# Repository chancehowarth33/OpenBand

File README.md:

<p align="center">
  <picture>
    <source media="(prefers-color-scheme: dark)" srcset="images/logo-dark.png">
    
  </picture>
</p>

<p align="center"><b>Open Source WHOOP.</b></p>

<p align="center">
  An open-source, screenless wearable health tracker built from scratch: custom PCB, custom
  firmware, custom enclosure, custom iOS app. It reads heart rate, blood oxygen, and steps off
  your wrist and streams them to your phone over Bluetooth.
</p>

---

## Why I built this

I wanted to know whether I could build a real consumer wearable end to end, by myself, rather
than wiring a dev board to a breakout sensor and calling it a project. That means every layer,
schematic capture, a two-layer board with an RF section that actually works, hand assembly,
bare-metal bring-up, an RTOS, sensor drivers written against datasheets, the signal processing
that turns raw photodiode counts into a heart rate, a Bluetooth GATT server, a printed
enclosure, and a native phone app to display it all.

WHOOP is the reference point because it has the same architecture as what I wanted to build: no
screen, no buttons, worn continuously on a strap, with all the intelligence in the sensors and
all the interface on your phone. That constraint is what makes it interesting. There is no
display to hide behind, so the device either produces trustworthy numbers or it does not.

It works. Heart rate, SpO2, steps, and battery all read correctly on hardware I designed and
soldered, and stream live to an app I wrote. Everything needed to build one is in this repo:
schematics, board layout, fabrication outputs, firmware, enclosure models, the full bill of
materials, and the iOS app.

### What it tracks

| Metric | Source | How |
|--------|--------|-----|
| **Heart rate** | MAX30102 PPG | Autocorrelation on the IR waveform (40–200 bpm band), quality-gated by perfusion index |
| **Blood oxygen (SpO2)** | MAX30102 PPG | Red/IR AC-to-DC ratio-of-ratios |
| **Steps** | BMI270 IMU | Onboard hardware step counter, with a software pedometer fallback |
| **Battery** | ADC divider | 100 kΩ / 220 kΩ divider off the LiPo rail |

All four stream to the phone over BLE every 2 seconds.

---

## The device

OpenBand is worn on the wrist with a standard strap. The electronics are a single ~38 mm
circular board that drops into a 3D-printed enclosure; the strap threads through slots on either
side, and four M1.6 screws retain the board from below. A cutout in the bottom of the case
exposes the optical sensor so it sits directly against the skin and has to be in firm, consistent contact with the wrist or the
pulse waveform disappears into noise.

The top shell holds the board in a circular pocket with a strap slot on each side. The bottom
retains it with four screws and exposes the MAX30102 window in the center.

The enclosure is OpenSCAD, in [`case/`](case), and went through two revisions. V1 taught me
most of what was wrong with it. The interior needed to be a true circle because the strap mounts
were intruding on the board pocket, the sensor window was slightly too small, the screw holes
were undersized for M1.6 threads, the programming-header opening did not line up with the pins,
and the outer wall of the strap slot was too thin to survive being worn. V2 fixed all of it.

---

## PCB design

A two-layer circular PCB, roughly 38 mm across, with a cutout at the bottom edge for strap
clearance and four mounting holes for the enclosure screws.

### 3D renders

**Front side.** The CYBLE-416045-02 BLE module dominates the center of the board with its MIFA
antenna exposed along the top edge, deliberately kept clear of copper pours for RF performance.
The BMI270 IMU sits bottom-left, the 32.768 kHz RTC crystal is top-left, and the LiPo charger IC
(U4_CHAR1), 1.8 V LDO (U5_1P8), and supporting passives are packed along the right edge. The SWD
programming header (JPROG1) and the battery/charger pads are on the left and bottom-right.

**Back side.** The MAX30102 optical heart rate and SpO2 sensor (U2_MAX1) is mounted on the back
of the board, facing down toward the skin when worn. Putting it on this side keeps the optical
window unobstructed and in direct contact with the wrist. Its decoupling capacitors are grouped
tightly around it to keep switching noise off the LED drive lines.

### Routing

**Front copper (F.Cu).** Red traces carry the I2C bus (SDA/SCL) from the CYBLE module out to the
BMI270 and down through vias to the MAX30102 on the back. The RTC lines route separately to
avoid crosstalk. Power distribution fans out from the LDO and charger on the right side.

**Back copper (B.Cu).** The back layer is kept deliberately sparse, primarily the I2C and power
connections to the MAX30102 plus the battery and charger fanout. The copper-free keepout under
the CYBLE module's antenna extends through both layers.

---

## Assembled hardware

**Bring-up ("proof of life").** The fully populated board running off a LiPo cell on the bench
with the green status LED lit. This was the first power-on test, confirming the CYBLE module,
LDO, and charger all came up correctly before any firmware was flashed.

**Size in hand.** The bare board for scale, with the battery leads attached.

**Assembled front.** The CYBLE-416045-02 and its gold MIFA antenna at the top, the BMI270 IMU
(U1_IMU1) and RTC crystal (RTC1) on the left, the SWD header (JPROG1) on the far left, and the
1.8 V LDO (U5_1P8) plus battery (BATT) and charger (CHAR) pads down the right side.

**Assembled back.** The skin-facing side, dominated by the MAX30102 optical HR/SpO2 sensor
(U2_MAX1) in the center, its window sitting flush against the wrist.

---

## Firmware

Built with **Infineon ModusToolbox** against the **CY8CPROTO-063-BLE** BSP (the same PSoC 6 BLE
part inside the CYBLE-416045-02 module), running **FreeRTOS**. Application code runs on the
Cortex-M4; the Cortex-M0+ runs the BLESS Bluetooth link-layer controller.

```
main.c
  └─ system_control_initialize()
       ├─ I2C init (SCB3, P6_4 SCL / P6_5 SDA, 400 kHz)
       ├─ i2c_mutex (recursive, shared by all sensor tasks)
       ├─ task_max30102        PPG FIFO → health_algo
       ├─ task_bmi270          6-axis IMU + hardware step counter
       ├─ task_sw_steps        software pedometer (SW_STEP_COUNTER builds only)
       ├─ task_system_control  prints health metrics every 2 s
       └─ task_ble             WICED BT stack + GATT notifications every 2 s
```

Both sensors share one 400 kHz I2C bus (MAX30102 at `0x57`, BMI270 at `0x68`), arbitrated by a
recursive mutex. Results land in `health_hr`, `health_spo2`, `health_steps`, and
`health_battery`, which the reporting and BLE tasks consume.

The parts I am most pleased with:

- **The signal processing runs on the device, not the phone.** `health_algo.c` does DC removal
  and moving-average smoothing, then finds heart rate by autocorrelation, looking for the
  strongest self-similarity lag in the 40 to 200 bpm band, with a threshold peak detector as a
  cross-check. A perfusion-index quality gate means a motion-corrupted window holds the last
  good value instead of confidently reporting garbage. SpO2 comes from the Red/IR ratio-of-ratios.
- **Power management is gated on the phone connection.** In `LOW_POWER` builds the optical
  sensor is fully shut down whenever no phone is connected, and runs live only while the app is
  connected, since HR and SpO2 only matter when someone is looking at them. Steps keep counting
  either way. With gyro-off, adaptive LED drive, shorter LED pulses, and slow BLE advertising and
  connection parameters, measured draw goes from about 12 mA to about 9 mA.
- **The step counter diagnoses itself.** The BMI270 needs an 8 KB configuration blob loaded over
  I2C at boot, which is by far the most demanding transfer on the bus, so the loader retries with
  a soft reset up to five times rather than bricking the task on a bad load. One of my boards
  appeared to have a dead feature engine, so I wrote a pure-software accelerometer pedometer
  (`SW_STEP_COUNTER`) as a drop-in replacement. The root cause turned out to be a cold solder
  joint, and re-reflowing the part fixed it, but the fallback stayed in.

Full detail, including the low-power measurements and the complete BMI270 debugging trail, is in
[`software/README.md`](software/README.md).

### BLE services

| Service | Characteristics |
|---------|-----------------|
| WatchWise Health (custom 128-bit) | SpO2 (read + notify), StepCount (read + notify, uint32 LE) |
| Heart Rate (`0x180D`) | HR Measurement (`0x2A37`) |
| Battery (`0x180F`) | Battery Level (`0x2A19`) |

Custom UUIDs: service `5E021176-5E66-483F-AE53-D3291D2CC787`, SpO2
`F1F72B4B-1D76-43A3-ADB2-0E04905ACC8F`, StepCount `C36072C1-2706-41F1-8D28-E0619FE31FFA`.

Heart rate and battery use the standard SIG-assigned services, so the device also works with any
generic BLE tool (nRF Connect shows it as `WatchWise2`) if you would rather not build the app.

---

## iOS app

A native **SwiftUI + CoreBluetooth** dashboard that auto-scans, connects, and streams live heart
rate, SpO2, steps, and battery, with a heart-rate trend line. It needs Xcode 16+ and a real
iPhone on iOS 17+, since BLE does not work in the Simulator. A free Apple ID is enough for 7-day
signing.

One detail worth mentioning: the firmware reports a *cumulative* step count that resets to zero
whenever the device reboots, so "today's steps" cannot just be the raw value. `StepTracker.swift`
tracks the counter's baseline and handles the reset case.

Build and signing steps are in
[`software/mobile/WatchWiseApp/README.md`](software/mobile/WatchWiseApp/README.md).

---

## Repository structure

```text
OpenBand/
├── pcb/                             # Board design
│   ├── altium_project/              # Altium project, schematic sheets, 3D
│   ├── watchwise_main_kicad/        # KiCad schematic + layout, JLCPCB outputs
│   └── assembly.txt                 # Assembly notes
│
├── software/
│   ├── README.md                    # Full firmware documentation
│   ├── firmware/                    # ModusToolbox firmware project
│   │   ├── Makefile                 # Build system, programming reset-pulse override
│   │   ├── bsps/                    # CY8CPROTO-063-BLE BSP + BT Configurator output
│   │   └── app/FreeRTOS/tasks/src/
│   │       ├── task_system_control.c    # I2C/UART init, task spawning, reporting
│   │       ├── task_max30102.c          # PPG driver + power scheduling
│   │       ├── task_bmi270.c            # IMU driver + hardware step counter
│   │       ├── sw_step_counter.c        # Software pedometer fallback
│   │       ├── task_ble.c               # WICED BT stack, GATT, notifications
│   │       ├── health_algo.c            # HR / SpO2 signal processing
│   │       └── ww_rtc.c                 # RTC
│   ├── mobile/WatchWiseApp/         # SwiftUI + CoreBluetooth iOS app
│   └── BMI270_debug.txt             # Step-counter investigation log
│
├── case/                            # OpenSCAD sources, STL, 3MF for the enclosure
├── devices/                         # Datasheets and reference material
│   ├── SoC/                         # CYBLE / PSoC 6 reference
│   ├── peripheral/                  # MAX30102, BMI270, MCP73831, LDO, battery
│   └── antenna/                     # Chip-antenna design guide
│
├── images/                          # Renders and photos used in this README
├── receipts/                        # DigiKey and JLCPCB orders
├── WatchWise-BOM.csv                # Bill of materials with DigiKey part numbers
└── interactive_BOM.html             # Clickable board view with component highlighting
```

---

## Bill of materials

Total BOM cost: **~$131.52** for a qty-3 order, so roughly **$44 per unit** in parts.

Open [`interactive_BOM.html`](interactive_BOM.html) in a browser for a clickable board view that
highlights each component in place. The full part list with DigiKey numbers is in
[`WatchWise-BOM.csv`](WatchWise-BOM.csv).

### ICs & modules

| Designator | Part | Description | DigiKey P/N |
|------------|------|-------------|-------------|
| U3_CYBLE1 | CYBLE-416045-02 | PSoC6 BLE module with integrated antenna (SMD) | 448-CYBLE-416045-02CT-ND |
| U2_MAX1 | MAX30102EFD+T | Optical heart rate and SpO2 sensor (I2C) | MAX30102EFD+TCT-ND |
| U1_IMU1 | BMI270 | 6-axis IMU, accelerometer and gyroscope (I2C/SPI) | 828-1091-1-ND |
| U4_CHAR1 | MCP73831T-2ACI/OT | Single-cell LiPo battery charger IC (SOT-23-5) | MCP73831T-2ACI/OTCT-ND |
| U5_1P8 | TLV70018DCKR | 1.8V LDO regulator, 200mA (SC-70-5) | 296-32409-1-ND |

### Indicators

| Designator | Part | Description | DigiKey P/N |
|------------|------|-------------|-------------|
| P_BATT1 | LTST-C281KGKT | Green LED, battery status indicator (0402) | 160-LTST-C281KGKTCT-ND |
| P_CHAR1 | VLMG1500-GS08 | Yellow-green LED, charge status indicator (0402) | VLMG1500-GS08CT-ND |

### Crystal

| Designator | Part | Description | DigiKey P/N |
|------------|------|-------------|-------------|
| RTC1 | MU00525-32.768K | 32.768 kHz crystal, 6pF load, SMD 3.2×1.5mm | 644-MU00525-32.768KCT-ND |

### Resistors

| Designator | Value | Description | DigiKey P/N |
|------------|-------|-------------|-------------|
| R1, R2, R3 | 4.7kΩ | I2C pull-ups (0402) | 311-4.7KJRCT-ND |
| R4, R_PWR1 | 10kΩ | General pull-up/down resistors (0402) | 311-10KJRCT-ND |
| RLED1 | 470Ω | LED current-limiting resistor (0402) | 311-470LRCT-ND |
| R_PROG1 | 47kΩ | MCP73831 charge-current programming resistor, sets ~21mA charge rate (0402) | 311-47.0KLRCT-ND |
| RD1 | 100kΩ | Battery voltage divider, lower leg (0402) | 311-100KLRCT-ND |
| RD2 | 220kΩ | Battery voltage divider, upper leg (0402) | 311-220KLRCT-ND |

> RD1 + RD2 form a resistor divider for ADC-based battery level sensing. R_PROG1 programs the
> MCP73831 charge current: I_CHG = 1000V / R_PROG(kΩ) ≈ 21mA.

### Capacitors

| Designator | Value | Package | Notes | DigiKey P/N |
|------------|-------|---------|-------|-------------|
| C1, C2, C4, C6, C10 | 0.1µF | 0402 | Bypass caps | 1276-1002-1-ND |
| C11, C12 | 1µF | 0402 | Bypass/decoupling | 399-C0402C105K9PACTUCT-ND |
| C3 | 4.7µF | 0402 | Decoupling, low-voltage rail | 1276-1482-1-ND |
| C13, C14 | 4.7µF | 0603 | Decoupling, BAT_OUT rail (3.7–4.2V); 0603 required to avoid derating | 1276-1044-1-ND |
| C9 | 10µF | 0603 | Bulk decoupling | 1292-0603X106M100CT-ND |
| C5 | 10µF | 0805 | Bulk decoupling, BAT_OUT rail (3.7–4.2V); 0805 required to avoid derating | 1276-1096-1-ND |
| C7, C8 | 6pF | 0402 | RTC crystal load capacitors | 490-3104-1-ND |

> C5, C13, and C14 are sized at 0805/0603 rather than 0402 because ceramic capacitance drops
> significantly under DC bias. Since BAT_OUT runs at 3.7 to 4.2 V, the larger packages are needed
> to hold rated capacitance.

---

## Build one

> The project was originally called WatchWise, and the source files, board files, and BLE device
> name still use that name. Only the project itself was renamed; nothing internal was touched.

**Boards.** KiCad sources and JLCPCB fabrication outputs are in
[`pcb/watchwise_main_kicad/`](pcb/watchwise_main_kicad); the Altium project is in
[`pcb/altium_project/`](pcb/altium_project). Order parts from
[`WatchWise-BOM.csv`](WatchWise-BOM.csv).

**Enclosure.** Print `watchwise_case_V2.stl` and `watchwise_case_strap.stl` from
[`case/`](case). You will need four M1.6 x 4 mm screws and a standard strap.

**Firmware.** From `software/firmware/`:

```bash
make getlibs      # First time only: pull .mtb dependencies
make build
make program      # Flash via KitProg3 over the JPROG1 SWD header
```

> **One required patch.** After the first `make getlibs`, apply
> [`software/patches/btstack-integration-bless-ipc-featuremask.patch`](software/patches). Infineon's
> `btstack-integration` requests a BLE feature mask that the prebuilt CM0+ controller binary
> rejects, so the stack silently fails to start. The firmware compiles either way, which means you
> only find out on hardware. [`software/patches/README.md`](software/patches/README.md) has the
> command and the full explanation.

Optional build flags, composable and off by default:

```bash
make program DEFINES=LOW_POWER                      # Sensor gating, gyro off, slow BLE
make program DEFINES=SW_STEP_COUNTER                # Software pedometer fallback
make program DEFINES="LOW_POWER SW_STEP_COUNTER"    # Both
```

Debug output is on UART P5_0/P5_1 at 115200 baud over the KitProg3 USB COM port.

> If `make program` fails with `acquire_psoc request failed`, press the JPROG1 pins in firmly and
> retry. JPROG1 has an RC filter on `XRES_N`, so the Makefile already widens the reset pulse; the
> BLE firmware sleeps the chip, so the reset has to catch it.

**Connect.** Open the iOS app, or scan with nRF Connect for `WatchWise2` and subscribe to the
SpO2 and StepCount notifications.

---

## Status and what is left

The prototype works end to end. Heart rate, SpO2, steps, and battery all read correctly and
stream live to the phone. What it is not yet is a device you would wear for a week without
thinking about it:

- **Battery life is the honest weak point.** About 5 hours on the 60 mAh cell in the default
  build, about 6.7 hours with `LOW_POWER`. The ceiling is the always-awake MCU, which is roughly
  78% of the ~12 mA baseline draw. Every other optimization is rearranging the remaining 22%.
- **Tickless deep sleep is the actual fix** and is not implemented yet. `Cy_SysPm_DeepSleep` plus
  FreeRTOS tickless idle should take idle draw from milliamps to microamps, projecting to roughly
  20 hours, and it is also what lets the BLE controller sleep between connection events. It needs
  careful handling of in-flight I2C, UART, and BLE transactions, so it is real work rather than a
  flag flip.
- **Off-wrist sleep** would push standby to days by using the IMU to notice the device is not
  being worn.
- **On-demand measurement over BLE.** Right now the phone connection itself is the trigger. A
  writable characteristic that requests a single measurement needs a GATT database change in BT
  Configurator.
- **No water resistance.** The enclosure is a printed shell with no gasket.

---

## License

Software and hardware are licensed separately, because copyright treats source code and design
files differently.

| What | License | Covers |
|------|---------|--------|
| **Software** | [MIT](LICENSE) | Firmware in `software/firmware/app/`, the iOS app in `software/mobile/` |
| **Hardware** | [CC BY 4.0](LICENSE-HARDWARE) | KiCad design in `pcb/watchwise_main_kicad/`, enclosure in `case/`, the BOM |

Both are permissive. Build one, modify it, sell it if you want. Just keep the attribution.

These licenses cover my original work only. This repo also contains third-party material that
stays under its own terms: the Infineon ModusToolbox BSP and Bluetooth stack, the FreeRTOS
kernel, Bosch's BMI270 configuration blob, and some UW-Madison ECE 453 course scaffolding. The
[NOTICE](NOTICE) file lists exactly what belongs to whom. Check it before redistributing,
since the Infineon terms in particular are more restrictive than MIT.

> **Not a medical device.** This is a personal prototype with no regulatory clearance. The heart
> rate and SpO2 numbers are not clinically validated and should not inform any health decision.

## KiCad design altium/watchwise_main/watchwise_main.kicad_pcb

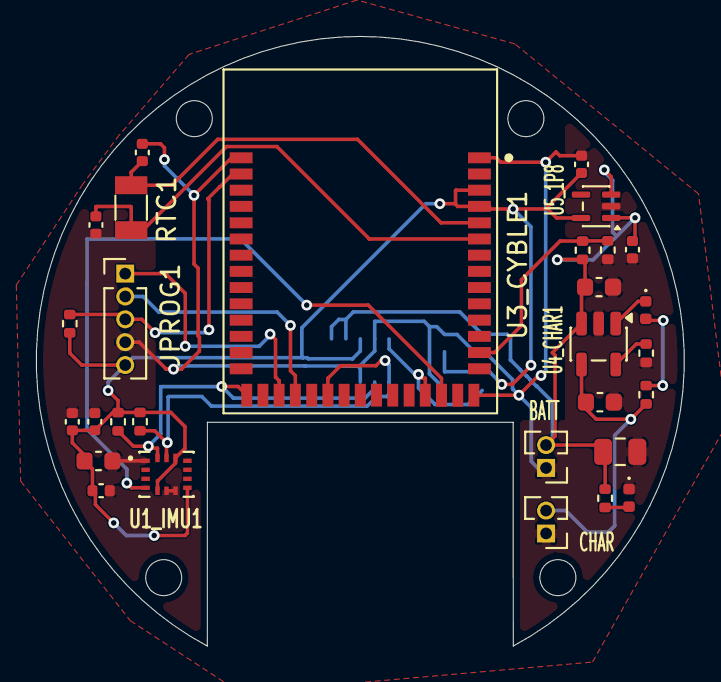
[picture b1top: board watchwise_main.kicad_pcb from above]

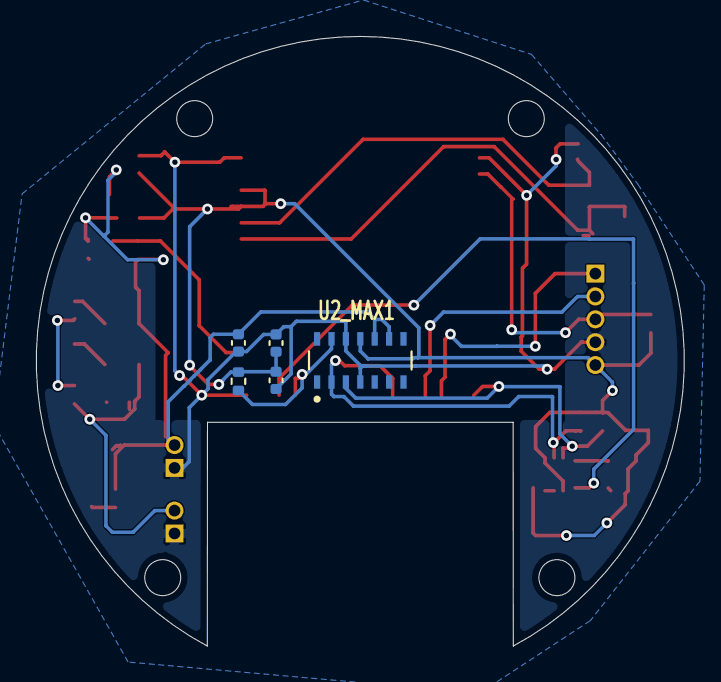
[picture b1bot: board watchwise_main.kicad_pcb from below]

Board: 2 copper layers, 36.0 x 33.9 mm, 34 parts (5 on the bottom side), 18 nets.

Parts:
BATT: J2 Battery; PinHeader_1x02_P1.27mm_Vertical
C1, C2, C4, C6, C10: 0.1uF; C_0402_1005Metric
C3: 4.7uF; C_0402_1005Metric
C5: 10uF; C_0805_2012Metric
C7, C8: 6pF; C_0402_1005Metric
C9: 10uF; C_0603_1608Metric
C11, C12: 1uF; C_0402_1005Metric
C13, C14: 4.7uF; C_0603_1608Metric
CHAR: J3 Charging; PinHeader_1x02_P1.27mm_Vertical
JPROG1: Prog; PinHeader_1x05_P1.27mm_Vertical
P_BATT1: LED; LED_0402_1005Metric
P_CHAR1: LED; LED_0402_1005Metric
R1, R2, R3: 4.7k; R_0402_1005Metric
R4: 10k; R_0402_1005Metric
RD1: 100k; R_0402_1005Metric
RD2: 220k; R_0402_1005Metric
RLED1: 0.47k; R_0402_1005Metric
RTC1: 32.768KHZ; Crystal_SMD_3215-2Pin_3.2x1.5mm
R_PROG1: 47k; R_0402_1005Metric
R_PWR1: 10k; R_0402_1005Metric
U1_IMU1: BMI270; XDCR_BMI270
U2_MAX1: MAX30102EFD_T; XDCR_MAX30101EFD_
U3_CYBLE1: CYBLE-416045-02
U4_CHAR1: MCP73831-2-OT; SOT-23-5
U5_1P8: TLV70018_SOT353; SOT-353_SC-70-5

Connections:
+1V8: C1.1, C2.1, C3.1, C4.1, C9.1, C10.1, C12.2, JPROG1.5, R1.1, R2.1, R3.1, R4.1, U1_IMU1.5 (VDDIO), U1_IMU1.8 (VDD), U1_IMU1.12 (CSB), U2_MAX1.11 (VDD), U3_CYBLE1.3 (VBACKUP), U3_CYBLE1.4 (VDD), U5_1P8.5 (OUT)
/RTC: C7.1, RTC1.1, U3_CYBLE1.5 (P0_0)
/RTC_N: C8.1, RTC1.2, U3_CYBLE1.6 (P0_1)
BAT_OUT: BATT.2, C5.1, C6.2, C11.2, C14.2, RD2.2, R_PWR1.1, U2_MAX1.9 (VLED+), U2_MAX1.10 (VLED+), U4_CHAR1.3 (V_{BAT}), U5_1P8.1 (IN), U5_1P8.3 (EN)
GND: BATT.1, C1.2, C2.2, C3.2, C4.2, C5.2, C6.1, C7.2, C8.2, C9.2, C10.2, C11.1, C12.1, C13.2, C14.1, CHAR.1, JPROG1.4, P_BATT1.1 (K), RD1.2, R_PROG1.2, U1_IMU1.1 (SDO), U1_IMU1.6 (GNDIO), U1_IMU1.7 (GND), U2_MAX1.4 (PGND), U2_MAX1.12 (GND), U3_CYBLE1.1 (GND), U3_CYBLE1.15 (GND), U3_CYBLE1.43 (GND), U4_CHAR1.2 (V_{SS}), U5_1P8.2 (GND)
INT_IMU: U1_IMU1.4 (INT1), U3_CYBLE1.17 (P9_0)
INT_MAX_N: R3.2, U2_MAX1.13 (~INT), U3_CYBLE1.18 (P9_1)
unnamed: C13.1, CHAR.2, RLED1.1, U4_CHAR1.4 (V_{DD})
unnamed: P_BATT1.2 (A), R_PWR1.2
unnamed: P_CHAR1.2 (A), RLED1.2
unnamed: P_CHAR1.1 (K), U4_CHAR1.1 (STAT)
unnamed: RD1.1, RD2.1, U3_CYBLE1.13 (P10_0)
unnamed: R_PROG1.1, U4_CHAR1.5 (PROG)
SCL: R2.2, U1_IMU1.13 (SCX), U2_MAX1.2 (SCL), U3_CYBLE1.24 (P6_4)
SDA: R1.2, U1_IMU1.14 (SDX), U2_MAX1.3 (SDA), U3_CYBLE1.29 (P6_5)
SWDCLK: JPROG1.2, U3_CYBLE1.26 (P6_7)
SWDIO: JPROG1.1, U3_CYBLE1.27 (P6_6)
XRES_N: JPROG1.3, R4.2, U3_CYBLE1.42 (~XRES)

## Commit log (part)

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2026-04-27 Updated ReadMe-2
2026-04-29 Update README.md
    added voltage regulator components
2026-04-30 fixed readme
2026-04-30 added software build steps to software file
2026-04-30 made vscode workspace
2026-04-30 All sensors up and printing out serial
2026-04-30 steps, co2, BMP added
2026-04-30 more accrate heartrate and CO2 and using the built insteps tracker in BMI
2026-04-30 update git ignore
2026-04-30 main changes
2026-04-30 update wuith main
2026-04-30 fixed power sheet
2026-05-01 schematic changes
2026-05-01 fixed errors with PCB
2026-05-01 pcb layout and battery
2026-05-01 clean
2026-05-01 removed USB-C, removed button, removed etra caps
2026-05-01 fixed LIPO circuit footprint
2026-05-01 added PCB cutout
2026-05-02 breaking down SoC module
2026-05-03 Changed whole footprint to 16.5 mm radius
2026-05-03 thru holes smaller and cleaned up placement
2026-05-03 Back to 18mm diameter, new battery ordered with dimenstions 4 x 12 x 15mm (T*W*L)
2026-05-03 flxed R_Prog value to be in the charging spec for battery
2026-05-04 Fixed cutout
2026-05-04 moved components around to reduce noise
2026-05-04 cleanup refdes
2026-05-05 routed but its shit
2026-05-05 no errors, with GND plane included
2026-05-05 NO ERRORS
2026-05-05 clean up, no DRC errors all done
2026-05-06 clean up
2026-05-06 Added V1 gerber files
2026-05-07 Gerber files and drill and BOM
2026-05-07 final
2026-05-07 All files completed
2026-05-07 Ignore watchwise backups folder
2026-05-07 removed backups
2026-05-09 cut out 17mm for battery
2026-05-09 fixed for demo
2026-05-11 fixes from merge to main
2026-05-13 routing all good no GND plane yet
2026-05-13 added voltage divider, need to clean up routing
2026-05-14 all routing done no errors, added voltage divider resistors
2026-05-14 fixing close traces
2026-05-14 all finished, error check passes
2026-05-14 changed some compnonets and added updated BOM with digikey links
2026-05-14 reverted caps back due to derating info, all files generated
2026-05-14 final rev, ordered PCB
2026-05-14 added digikey order info
2026-05-15 update readme and add 3D models for chips
2026-05-15 Remove backup/temp files and add to .gitignore
2026-05-29 added BMI270 receipt
2026-05-29 Add BLE task with WICED BT stack for SpO2 and step-count notifications and Heartrate
2026-05-30 BLE connected, no serivces tho
2026-05-31 heartrate BLE works
2026-06-01 fixed BLE issue, added bat life % to BLE output
2026-06-04 changes to make programming and serial monitor correct
2026-06-04 added case
2026-06-11 name changes and touch ups
2026-06-20 redesign of case
2026-06-22 finished case with strap holes
2026-06-23 working case that fits enitre board snug. No battery mount yet
2026-06-29 added low power mode and interctive BOM
2026-06-29 added clickable link in readME of interactive BOM
2026-06-29 moved BOM to top level of repo
2026-06-29 added logo to app
2026-06-29 changes to firm and soft for more tracking
2026-06-30 app: DIS serial, today's-steps (Option A), auto-connect fix, 0-as-no-reading
